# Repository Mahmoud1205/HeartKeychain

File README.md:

# Heart Keychain
Project for HC Stasis Program.

I made this keychain as a gift to someone, I wanted to make it as a PCB because I was finally confident in my PCB design and fabrication skills after my progress in the [Athan Lamp project](https://github.com/Mahmoud1205/AthanLamp).

## BOM
| # | Sourced | References  | Value        | Footprint                                                     | Quantity |
|---|---------|-------------|--------------|---------------------------------------------------------------|----------|
| 1 |         | R1, R2, R3  | R_US         | R_Axial_DIN0207_L6.3mm_D2.5mm_P7.62mm_Horizontal              | 3        |
| 2 |         | D1, D2, D3  | LED          | LED_D3.0mm                                                    | 3        |
| 3 |         | SW1         | SW_Push      | SW_PUSH_6mm_H5mm                                              | 1        |
| 4 |         | BT1         | Battery_Cell | BatteryHolder_MYOUNG_BS-07-A1BJ001_CR2032                     | 1        |

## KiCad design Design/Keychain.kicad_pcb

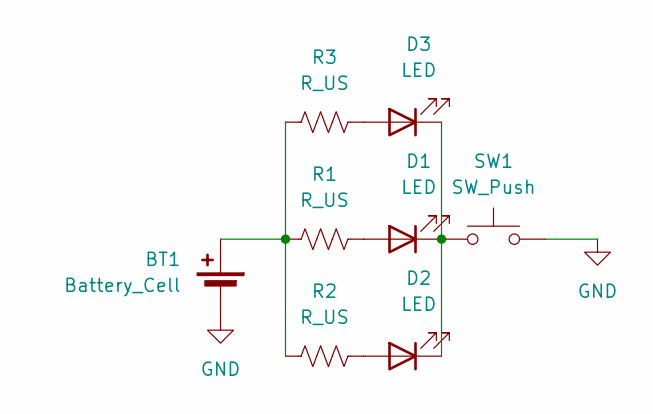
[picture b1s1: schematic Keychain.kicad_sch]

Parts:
BT1: Battery_Cell; BatteryHolder_MYOUNG_BS-07-A1BJ001_CR2032
D1, D2, D3: LED; LED_D3.0mm
R1, R2, R3: R_US; R_Axial_DIN0207_L6.3mm_D2.5mm_P7.62mm_Horizontal
SW1: SW_Push; SW_PUSH_6mm_H5mm

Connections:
GND: BT1.2 (-), SW1.2
unnamed: BT1.1 (+), R1.1, R2.1, R3.1
unnamed: D1.2 (A), R1.2
unnamed: D1.1 (K), D2.1 (K), D3.1 (K), SW1.1
unnamed: D2.2 (A), R2.2
unnamed: D3.2 (A), R3.2

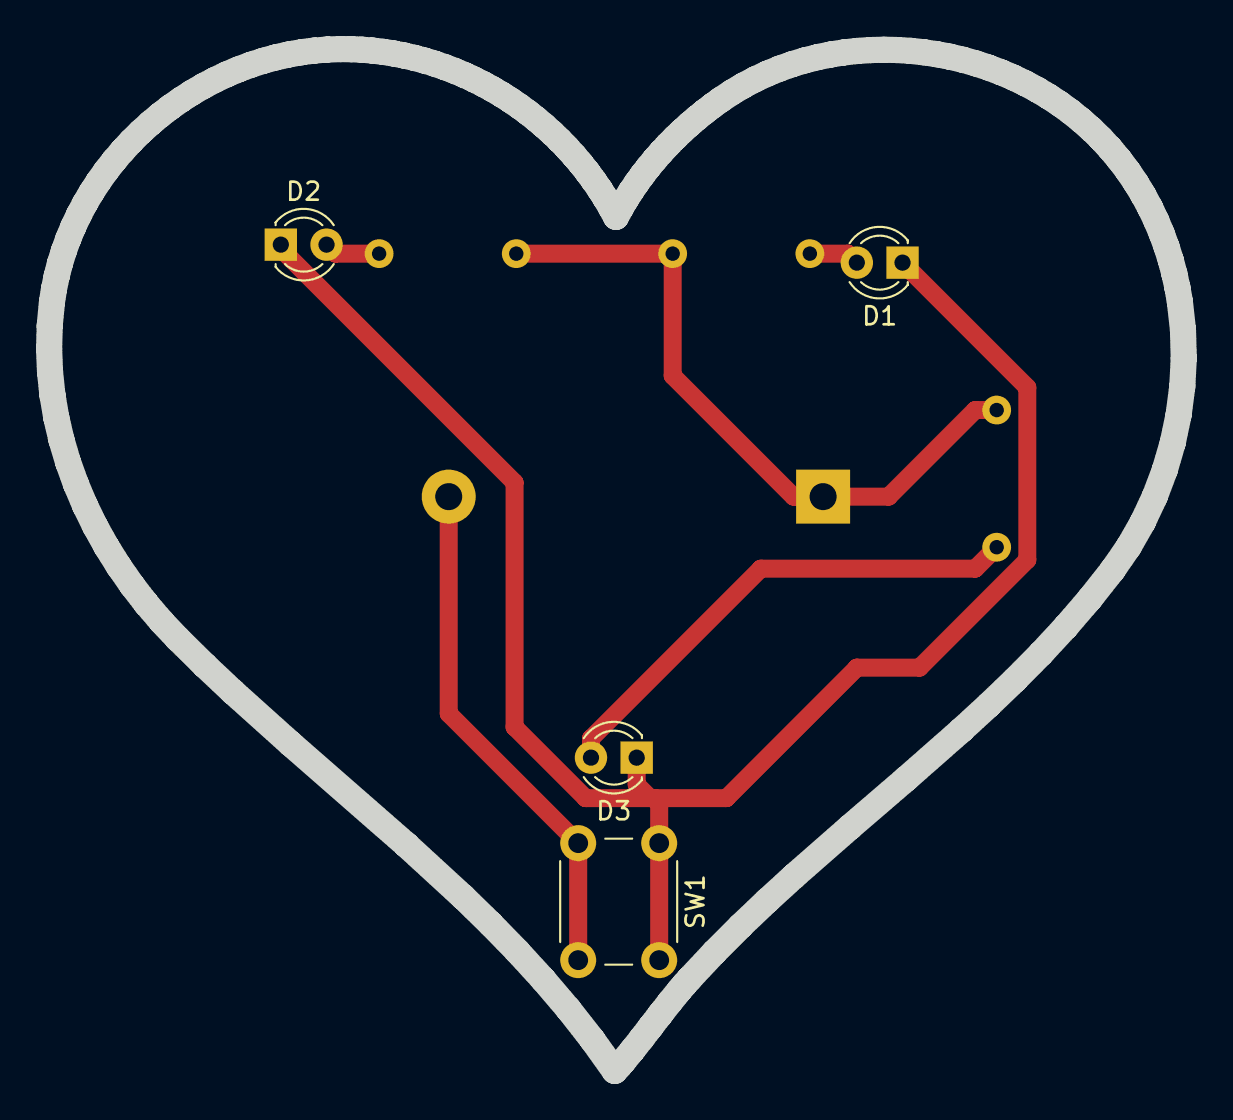
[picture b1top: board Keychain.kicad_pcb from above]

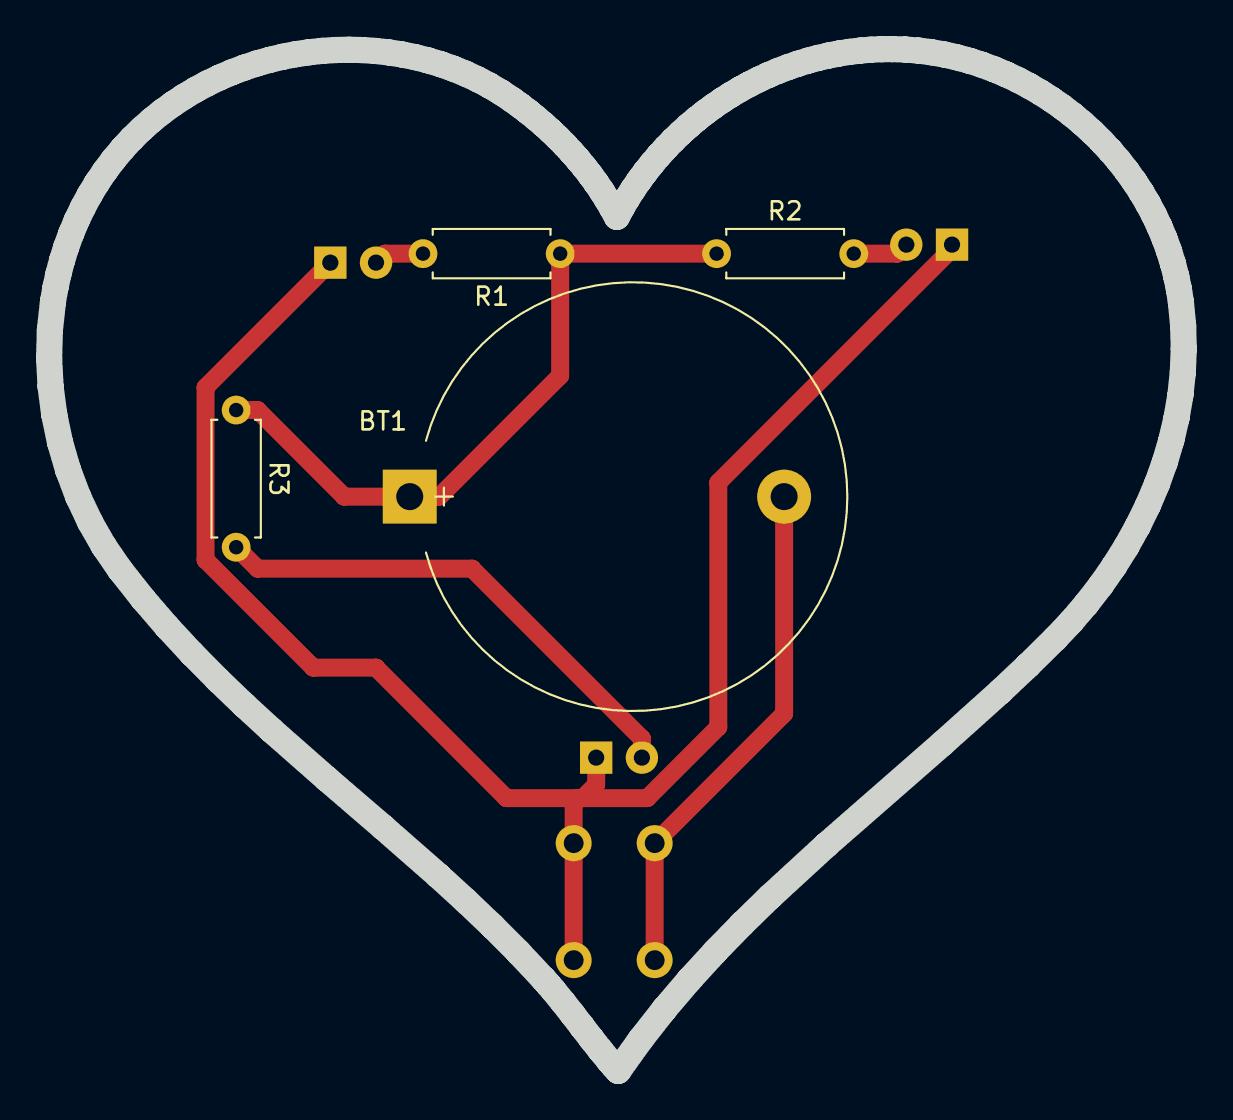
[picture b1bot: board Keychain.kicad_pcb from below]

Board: 2 copper layers, 63.0 x 56.8 mm, 8 parts (4 on the bottom side), 6 nets.

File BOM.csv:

"","Sourced","References","Value","Footprint","Quantity"
1,"","R1, R2, R3","R_US","R_Axial_DIN0207_L6.3mm_D2.5mm_P7.62mm_Horizontal",3
2,"","D1, D2, D3","LED","LED_D3.0mm",3
3,"","SW1","SW_Push","SW_PUSH_6mm_H5mm",1
4,"","BT1","Battery_Cell","BatteryHolder_MYOUNG_BS-07-A1BJ001_CR2032",1

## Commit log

2026-04-25 add image and gif
2026-04-25 add more info to README and BOM
2026-05-05 add pcb production file
